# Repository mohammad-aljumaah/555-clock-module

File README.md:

# 555 Clock Module

Designed by **Mohammad Aljumaah** · [mohammad-aljumaah.me](https://mohammad-aljumaah.me)

A simple clock pulse generator built with the NE555P timer IC.
Outputs a ~7 Hz square wave. useful for clocking counters, shift registers, and other digital circuits.

Designed from scratch in KiCad. Includes schematic, PCB layout, Gerbers, and a full datasheet.

---

## Specs

| | |
|---|---|
| Supply | 5 V DC |
| Output | ~7 Hz square wave, ~50% duty cycle |
| Connector | 3-pin header — GND / VCC / CLK_OUT |
| Main IC | NE555P (DIP-8) |
| PCB | 2-layer, 4× M3 mounting holes |

---

## Repo Structure

```
Documentation/
├── datasheet.pdf       ← Full datasheet with specs, BOM, pinout, and theory
└── schematic.pdf       ← Exported schematic

Hardware/
├── 555-timer-clock.kicad_sch
├── 555-timer-clock.kicad_pcb
└── 555-timer-clock.kicad_pro

Production/
├── Gerbers/            ← Ready to send to a PCB fab
└── ZIP/
    └── 555-timer-clock-rA.zip   ← Zipped Gerbers, ready to upload
```

---

## Ordering a PCB

Upload `Production/ZIP/555-timer-clock-rA.zip` to any PCB fab:

- [JLCPCB](https://jlcpcb.com)
- [PCBWay](https://pcbway.com)
- [OSH Park](https://oshpark.com)

Recommended: **2 layers · FR-4 · 1.6 mm · HASL**

---

## Documentation

See [`Documentation/datasheet.pdf`](Documentation/datasheet.pdf) for the full datasheet. includes BOM, pinout, how to use it, how to change the speed, and safety notes.

---

**Mohammad Aljumaah** · [mohammad-aljumaah.me](https://mohammad-aljumaah.me)

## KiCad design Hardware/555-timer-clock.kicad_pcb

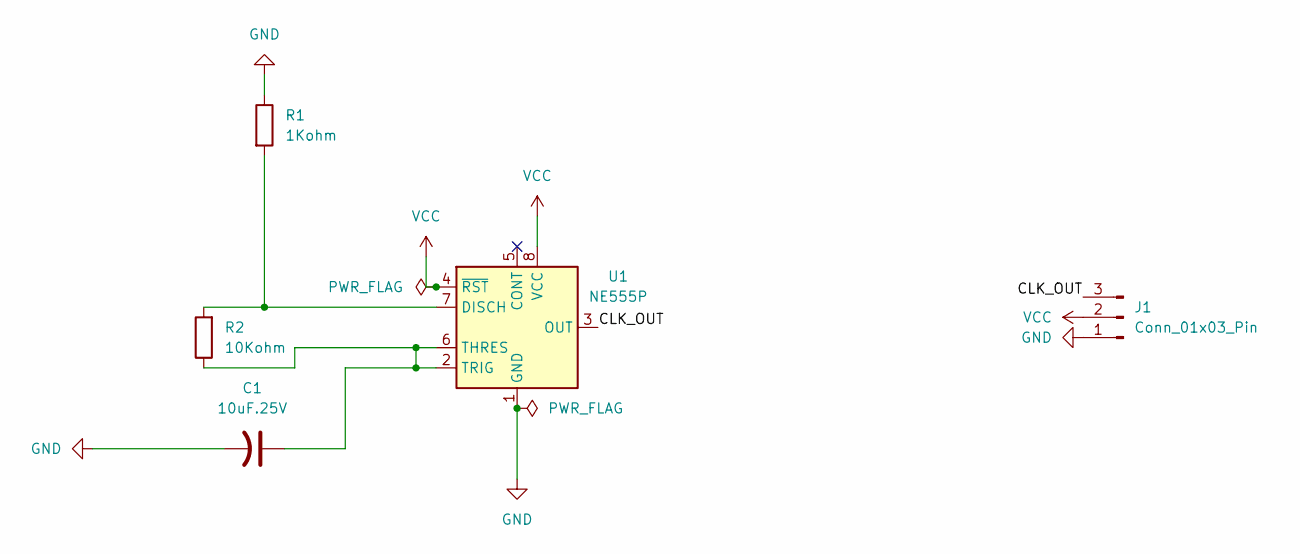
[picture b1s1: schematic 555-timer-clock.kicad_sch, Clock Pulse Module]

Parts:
C1: 10uF.25V; CP_Radial_D4.0mm_P2.00mm
J1: Conn_01x03_Pin; PinHeader_1x03_P2.54mm_Vertical
R1: 1Kohm; R_Axial_DIN0207_L6.3mm_D2.5mm_P7.62mm_Horizontal
R2: 10Kohm; R_Axial_DIN0207_L6.3mm_D2.5mm_P7.62mm_Horizontal
U1: NE555P; DIP-8_W7.62mm

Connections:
/CLK_OUT: J1.3, U1.3 (OUT)
GND: C1.2, J1.1, R1.1, U1.1 (GND)
unnamed: R1.2, R2.2, U1.7 (DISCH)
unnamed: C1.1, R2.1, U1.2 (TRIG), U1.6 (THRES)
VCC: J1.2, U1.4 (~RST), U1.8 (VCC)

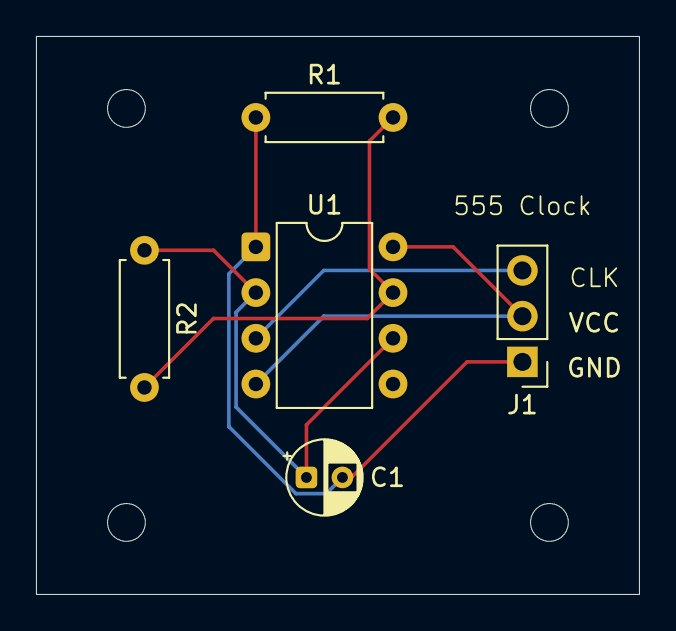
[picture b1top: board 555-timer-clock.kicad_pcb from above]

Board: 2 copper layers, 33.5 x 31.0 mm, 5 parts (0 on the bottom side), 5 nets.

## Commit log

2026-06-25 Rename 555-timer-clock.pdf to schematic.pdf
2026-06-25 Rename 555-clock-datasheet.pdf to datasheet.pdf
